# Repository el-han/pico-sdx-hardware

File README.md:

# Pico SDX

Pico SDX is a Software Defined HF Transceiver.

## Related Projects

- [uSDX](https://github.com/threeme3/usdx): ATmega 328P based SSB Transceiver. Large Arduino source file, no hardware sources, only schematics
- [(tr)uSDX](https://dl2man.de/): Implementation of uSDX by DL2MAN. No hardware sources, only schematics
- [uSDX-x](https://github.com/KD9PDP/uSDX-x): uSDX implementation with KiCAD hardware sources and JLCPCB friendly manufacturing data. ATmega328P based and compatible to uSDX. **Looks like a good starting point**
- [uSDR-pico](https://github.com/ArjanteMarvelde/uSDR-pico): RP2040 based SSB Transceiver. Highly experimental according to author. Pico SDK based Firmware, Eagle hardware sources. **Looks like a good starting point**
- [Blueberry SDR](http://www.andreadrian.de/sdr/Blueberry_SDR_schematics.html) experiments with different designs and components
- [YU1MLs SDRs](https://web.archive.org/web/20200227193146/http://yu1lm.qrpradio.com/sdr%20rx%20yu1lm.htm) many RX, TX and TRX designs
- [Teensy SDR](https://www.pjrc.com/convolution-software-defined-radio/) Teensy based sdr with waterfall diagram

## Related resources

- [Barbaros Aşuroğlu](https://antrak.org.tr/author/barbarosasuroglu/) has built an own uSDX implementation and many other projects.
- [QRP labs](https://www.qrp-labs.com/lpfkit.html) sells low pass and band pass filter modules for all HF bands
- [QRP labs](https://www.qrp-labs.com/synth/ms5351m.html) comparison between the clock generators Si5351A (Silicon labs) and MS5351M (Relmon) regarding usage in SDRs
- [Calculate your locator](https://dxcluster.ha8tks.hu/hamgeocoding/)

## technical background

- [Dan Tayloe](https://www.norcalqrp.org/files/Tayloe_mixer_x3a.pdf) brief description of the operation of quadratur mixers
- Gerald Youngbloods QEX articles [1](https://www.arrl.org/files/file/Technology/tis/info/pdf/020708qex013.pdf), [2](https://www.arrl.org/files/file/Technology/tis/info/pdf/020910qex010.pdf), [3](https://www.arrl.org/files/file/Technology/tis/info/pdf/021112qex027.pdf) and [4](http://www.arrl.org/files/file/Technology/tis/info/pdf/030304qex020.pdf) very good, detailed and comprehensive description of SDR projects for ham radio operators and additional [ARRL SDR](http://www.arrl.org/software-defined-radio) resources
- Walla Walla University projects: [Paper](http://fweb.wallawalla.edu/~frohro/ClassHandouts/Electronics/A%20Comparison%20of%20Affordable,%20Self-Assembled%20%20Software-Defined%20Radio%20Receivers%20Using%20Quadrature%20Sampling%20Down-Conversion.pdf), [Talk](https://www.youtube.com/watch?v=UoL1Qzaw2H0&t=217s),[Jordyn Watkins Wiki](https://github.com/greenjacketgirl/SDR_Receiver/wiki), [Caleb Froelichs Wiki](https://github.com/froeca/Software-Defined-Radio/), [Konrad MacClure](https://github.com/KonradMcClure/SDR_Receiver) and [SMD Version by Caleb Nelson](https://github.com/Dizzerin/Software-Defined-Radio)with detailed explanations, simulations, design decisions and tests
- [Burkhard Kainkas](https://www.b-kainka.de/iqrx.htm) experiments with iq mixers
- [devttys0](https://www.youtube.com/watch?v=JuuKF1RFvBM) video on explanations of the function of the tayloe mixer
- [w2aew](https://www.youtube.com/watch?v=Mm7WfVzr1ao) video on RF-mixer basics
- [BPF design for HF-Tranceiver](https://www.arrl.org/files/file/Technology/tis/info/pdf/8809017.pdf)
- [devttys0](https://www.youtube.com/watch?v=1sq8Cvju2Oo) video on practical filter design and construction

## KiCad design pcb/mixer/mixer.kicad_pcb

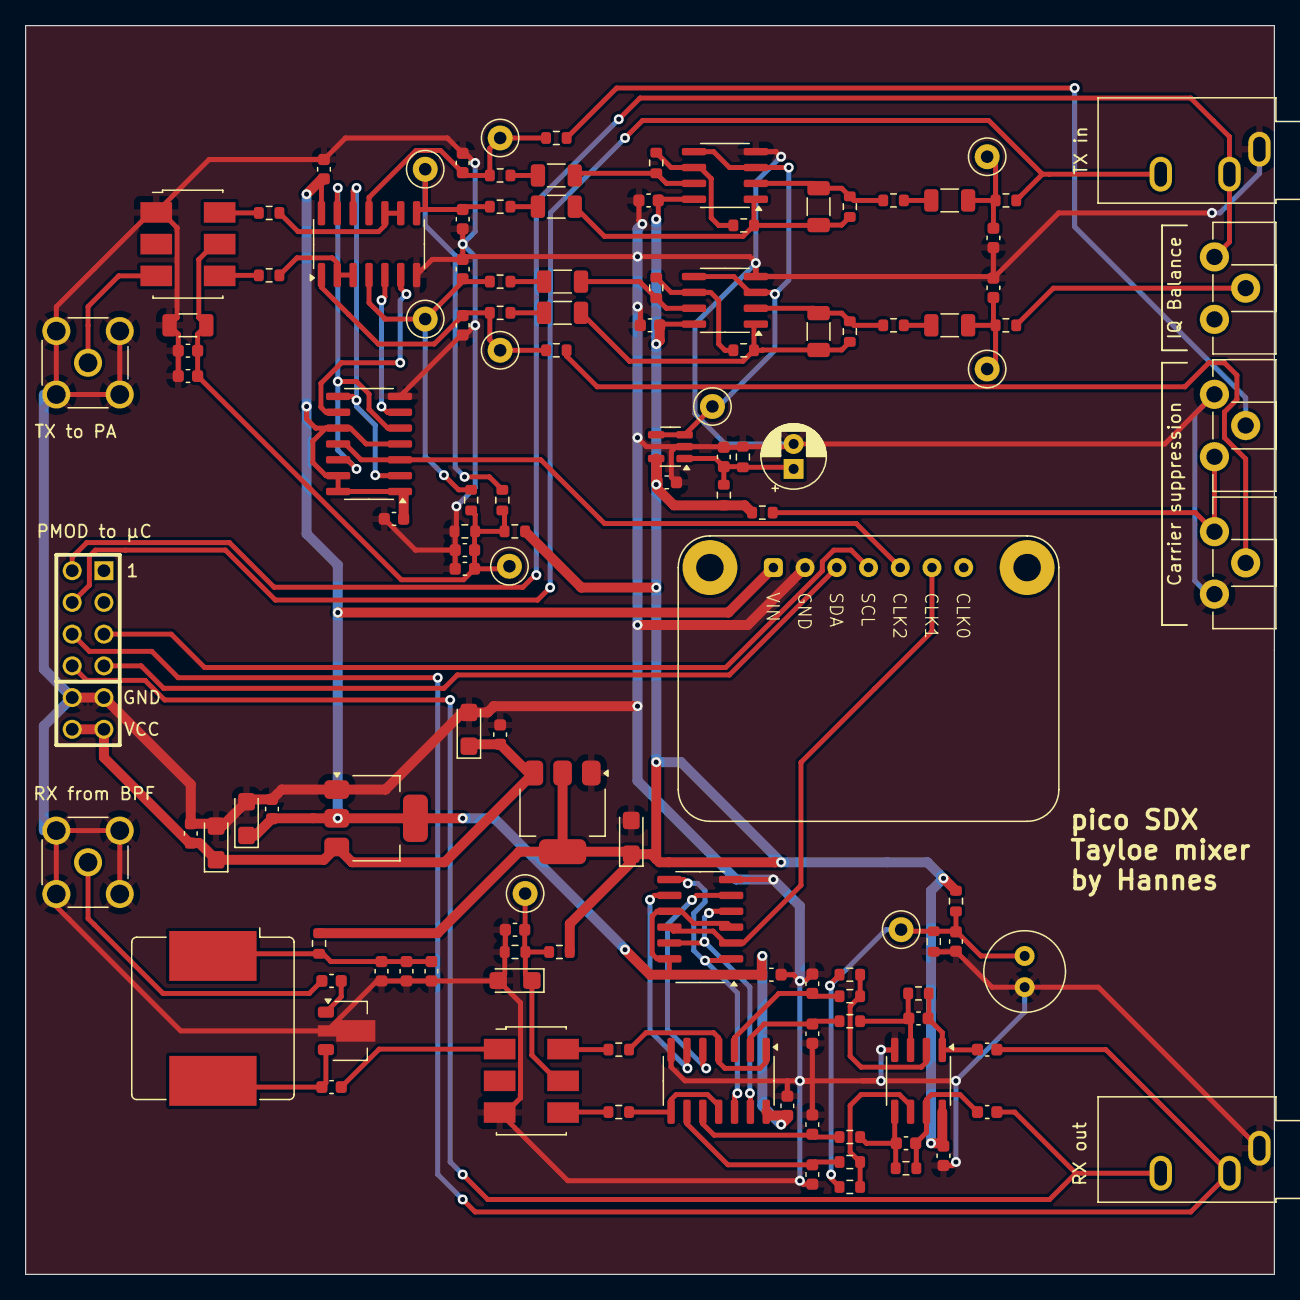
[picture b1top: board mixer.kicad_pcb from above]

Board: 2 copper layers, 100.0 x 100.0 mm, 126 parts (0 on the bottom side), 73 nets.

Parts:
C1, C2, C7, C14, C17, C19, C20, C32, C38, C39, C40, C42, C43, C44, C45, C51: 100nF; C_0603_1608Metric
C3, C4, C5, C6, C21: 1µF; CP_EIA-3216-18_Kemet-A
C8, C9, C10, C11, C33, C34, C35, C36: 22nF; C_0603_1608Metric
C12, C13: 330pF; C_0603_1608Metric
C15, C16, C46, C50: 1µF; C_0603_1608Metric
C18, C41: 10nF; C_0603_1608Metric
C22: 330µF; C_Radial_D6.3mm_H11.0mm_P2.50mm
C23, C24: 220pF; C_0603_1608Metric
C25, C26, C27, C28, C29, C30, C37: 10µF; C_1206_3216Metric
C31: 47µF; CP_Radial_D5.0mm_P2.00mm
C47: 2.2µF; C_0603_1608Metric
C48: 1000pF; C_0603_1608Metric
C49: 100pF; C_0603_1608Metric
C52, C53: 100pF; C_1206_3216Metric
J4, J5: Conn_Coaxial; SMA_Molex_73251-2200_Horizontal
J6, J7: AudioJack3; Jack_3.5mm_CUI_SJ1-3533NG_Horizontal
L1: 27µH; L_Bourns_SRR1208_12.7x12.7mm
P1: PMOD-Device-x2-Type-Generic-Alt; pmod_pin_array_6x2
R1, R2: 82R; R_0603_1608Metric
R3, R4, R5, R6: 100R; R_0603_1608Metric
R7, R8, R9, R10, R15, R29, R30, R31, R32, R34, R35: 2.2k; R_0603_1608Metric
R11, R12, R13, R14: 1k; R_0603_1608Metric
R16: 2.7k; R_0603_1608Metric
R17, R18, R19, R20, R25, R26, R37, R38: 10k; R_0603_1608Metric
R21, R22, R23, R24: 51R; R_0603_1608Metric
R27, R28: 47R; R_0603_1608Metric
R33: 1.2k; R_0603_1608Metric
R36: 1.8R; R_0603_1608Metric
R39, R40: 7.5k; R_0603_1608Metric
RV1, RV2, RV3: 1k; Potentiometer_Piher_PT-10-H01_Horizontal
T1: T-622; Transformer_MiniCircuits_ADT1-6T+
T2: Transformer_SP_1S; Transformer_MiniCircuits_ADT1-6T+
TP3: RX_TR_Midpoint; TestPoint_Loop_D1.80mm_Drill1.0mm_Beaded
TP4: RX_OPAMP_Midpoint; TestPoint_Loop_D1.80mm_Drill1.0mm_Beaded
TP5, TP6, TP7, TP8, TP9, TP10, TP11, TP12: TestPoint; TestPoint_Loop_D1.80mm_Drill1.0mm_Beaded
U1: Module_Si5351
U5: LT1117-5.0; SOT-223-3_TabPin2
U6, U9: 74HC74; SOIC-14_3.9x8.7mm_P1.27mm
U7, U12: 4066; SOIC-14_3.9x8.7mm_P1.27mm
U8: OPA2350; SOIC-8_3.9x4.9mm_P1.27mm
U10, U14: OPA1602; SOIC-8_3.9x4.9mm_P1.27mm
U11: LM321; SOT-23-5
U13: HMC589A; SOT-89-3
U17: LT1117-3.3; SOT-223-3_TabPin2

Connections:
+3.3V: C5.1, C7.1, C14.1, C17.1, C40.1, C42.1, U1.1 (VIN), U6.1 (~R), U6.4 (~S), U6.10 (~S), U6.13 (~R), U6.14 (VCC), U7.14 (VDD), U9.1 (~R), U9.4 (~S), U9.10 (~S), U9.13 (~R), U9.14 (VCC), U12.14 (VDD), U17.2 (VO)
+5VA: C6.1, C20.1, C38.1, C44.1, C51.1, R11.1, R13.1, R25.1, R31.1, R33.1, R36.2, U5.2 (VO), U8.8 (V+), U10.8 (V+), U11.5 (V+), U14.8 (V+)
+12V: C1.1, C2.1, C3.1, C4.1, P1.6, P1.12, U5.3 (VI), U17.3 (VI)
/Buffer Amplifier/RF in: C46.1, J4.1 (In)
/Buffer Amplifier/RF out: C50.2, T1.1 (Primary)
/Downconverter/2.5V_OPAMP: C19.1, C22.1, R8.2, R10.2, R13.2, R14.1, TP4.1
/Downconverter/2.5V_TR: C18.1, C21.1, R11.2, R12.1, T1.5 (Secondary_CT), TP3.1
/Downconverter/CLK_I: U6.5 (Q), U6.12 (D), U7.13
/Downconverter/CLK_Q: U6.9 (Q), U7.6
/Downconverter/~CLK_I: U6.6 (~Q), U7.5
/Downconverter/~CLK_Q: U6.2 (D), U6.8 (~Q), U7.12
/Upconverter/2.5V: TP11.1, U10.3 (+), U10.5 (+), U11.3 (-), U11.4, U14.3 (+), U14.5 (+)
/Upconverter/BIAS: C37.1, C39.1, C41.1, C43.1, C45.1, R30.2, R31.2, R32.1, R34.1, T2.5 (Secondary_CT), TP12.1
/Upconverter/BIAS_I: C33.1, R21.2, R29.1, TP7.1, U12.1
/Upconverter/BIAS_Q: C35.1, R23.2, R34.2, TP9.1, U12.8
/Upconverter/CLK_I: U9.5 (Q), U9.12 (D), U12.13
/Upconverter/CLK_Q: U9.9 (Q), U12.6
/Upconverter/TX_OUT: J5.1 (In), T2.3 (Primary_dot)
/Upconverter/~BIAS_I: C34.1, R22.2, R30.1, TP8.1, U12.4
/Upconverter/~BIAS_Q: C36.1, R24.2, R35.2, TP10.1, U12.11
/Upconverter/~CLK_I: U9.6 (~Q), U12.5
/Upconverter/~CLK_Q: U9.2 (D), U9.8 (~Q), U12.12
GND: C1.2, C2.2, C3.2, C4.2, C5.2, C6.2, C7.2, C8.1, C9.1, C10.1, C11.1, C14.2, C17.2, C18.2, C19.2, C20.2, C21.2, C22.2, C23.2, C24.2, C31.2, C32.2, C33.2, C34.2, C35.2, C36.2, C37.2, C38.2, C39.2, C40.2, C41.2, C42.2, C43.2, C44.2, C45.2, C47.2, C48.2, C49.2, C51.2, J4.2 (Ext), J5.2 (Ext), J6.S, J7.S, P1.5, P1.11, R12.2, R14.2, R26.2, R32.2, RV2.3, RV3.1, T1.3 (Primary_dot), T2.1 (Primary), U1.2 (GND), U5.1 (GND), U6.7 (GND), U7.7 (VSS), U8.4 (V-), U9.7 (GND), U10.4 (V-), U11.2 (V-), U12.7 (VSS), U13.2 (GND), U14.4 (V-), U17.1 (GND)
unnamed: C8.2, R3.1, U7.2
unnamed: C9.2, R4.1, U7.3
unnamed: C10.2, R5.1, U7.10
unnamed: C11.2, R6.1, U7.9
unnamed: C12.1, C15.2, R7.2, U8.1
unnamed: C13.1, C16.2, R9.2, U8.7
unnamed: C23.1, C25.1, R15.2, TP5.1
unnamed: C24.1, C26.1, R16.2, TP6.1
unnamed: C25.2, R39.1
unnamed: C26.2, R40.1
unnamed: C27.1, C52.2, R17.1, R38.2, U10.1
unnamed: C27.2, R21.1
unnamed: C28.1, R19.2, U10.7
unnamed: C28.2, R22.1
unnamed: C29.1, C53.2, R18.1, R37.2, U14.1
unnamed: C29.2, R23.1
unnamed: C30.1, R20.2, U14.7
unnamed: C30.2, R24.1
unnamed: C46.2, U13.1
unnamed: C47.1, C48.1, C49.1, L1.1, R36.1
unnamed: C50.1, L1.2, U13.3
unnamed: R1.1, T1.6 (Secondary_dot)
unnamed: R1.2, U7.1, U7.4
unnamed: R2.1, T1.4 (Secondary_dot)
unnamed: R2.2, U7.8, U7.11
unnamed: R15.1, RV1.2
unnamed: R27.1, U12.2, U12.3
unnamed: R27.2, T2.4 (Secondary_dot)
unnamed: R28.1, U12.9, U12.10
unnamed: R28.2, T2.6 (Secondary_dot)
unnamed: R29.2, RV2.2
unnamed: R33.2, RV2.1, RV3.3
unnamed: R35.1, RV3.2
unnamed: C12.2, R3.2, R7.1, U8.3 (+)
unnamed: R4.2, R8.1, U8.2 (-)
unnamed: C13.2, R5.2, R9.1, U8.5 (+)
unnamed: R6.2, R10.1, U8.6 (-)
unnamed: C52.1, R38.1, R39.2, U10.2 (-)
unnamed: R17.2, R19.1, U10.6 (-)
unnamed: C31.1, C32.1, R25.2, R26.1, U11.1 (+)
unnamed: C53.1, R37.1, R40.2, U14.2 (-)
unnamed: R18.2, R20.1, U14.6 (-)
RX_I: C15.1, J6.T, P1.9
RX_LO: U1.6 (CLK1), U6.3 (C), U6.11 (C)
RX_Q: C16.1, J6.R, P1.10
SCL: P1.3, U1.4 (SCL)
SDA: P1.4, U1.3 (SDA)
TX_I: J7.T, P1.7, RV1.1
TX_LO: U1.5 (CLK2), U9.3 (C), U9.11 (C)
TX_Q: J7.R, P1.8, R16.1

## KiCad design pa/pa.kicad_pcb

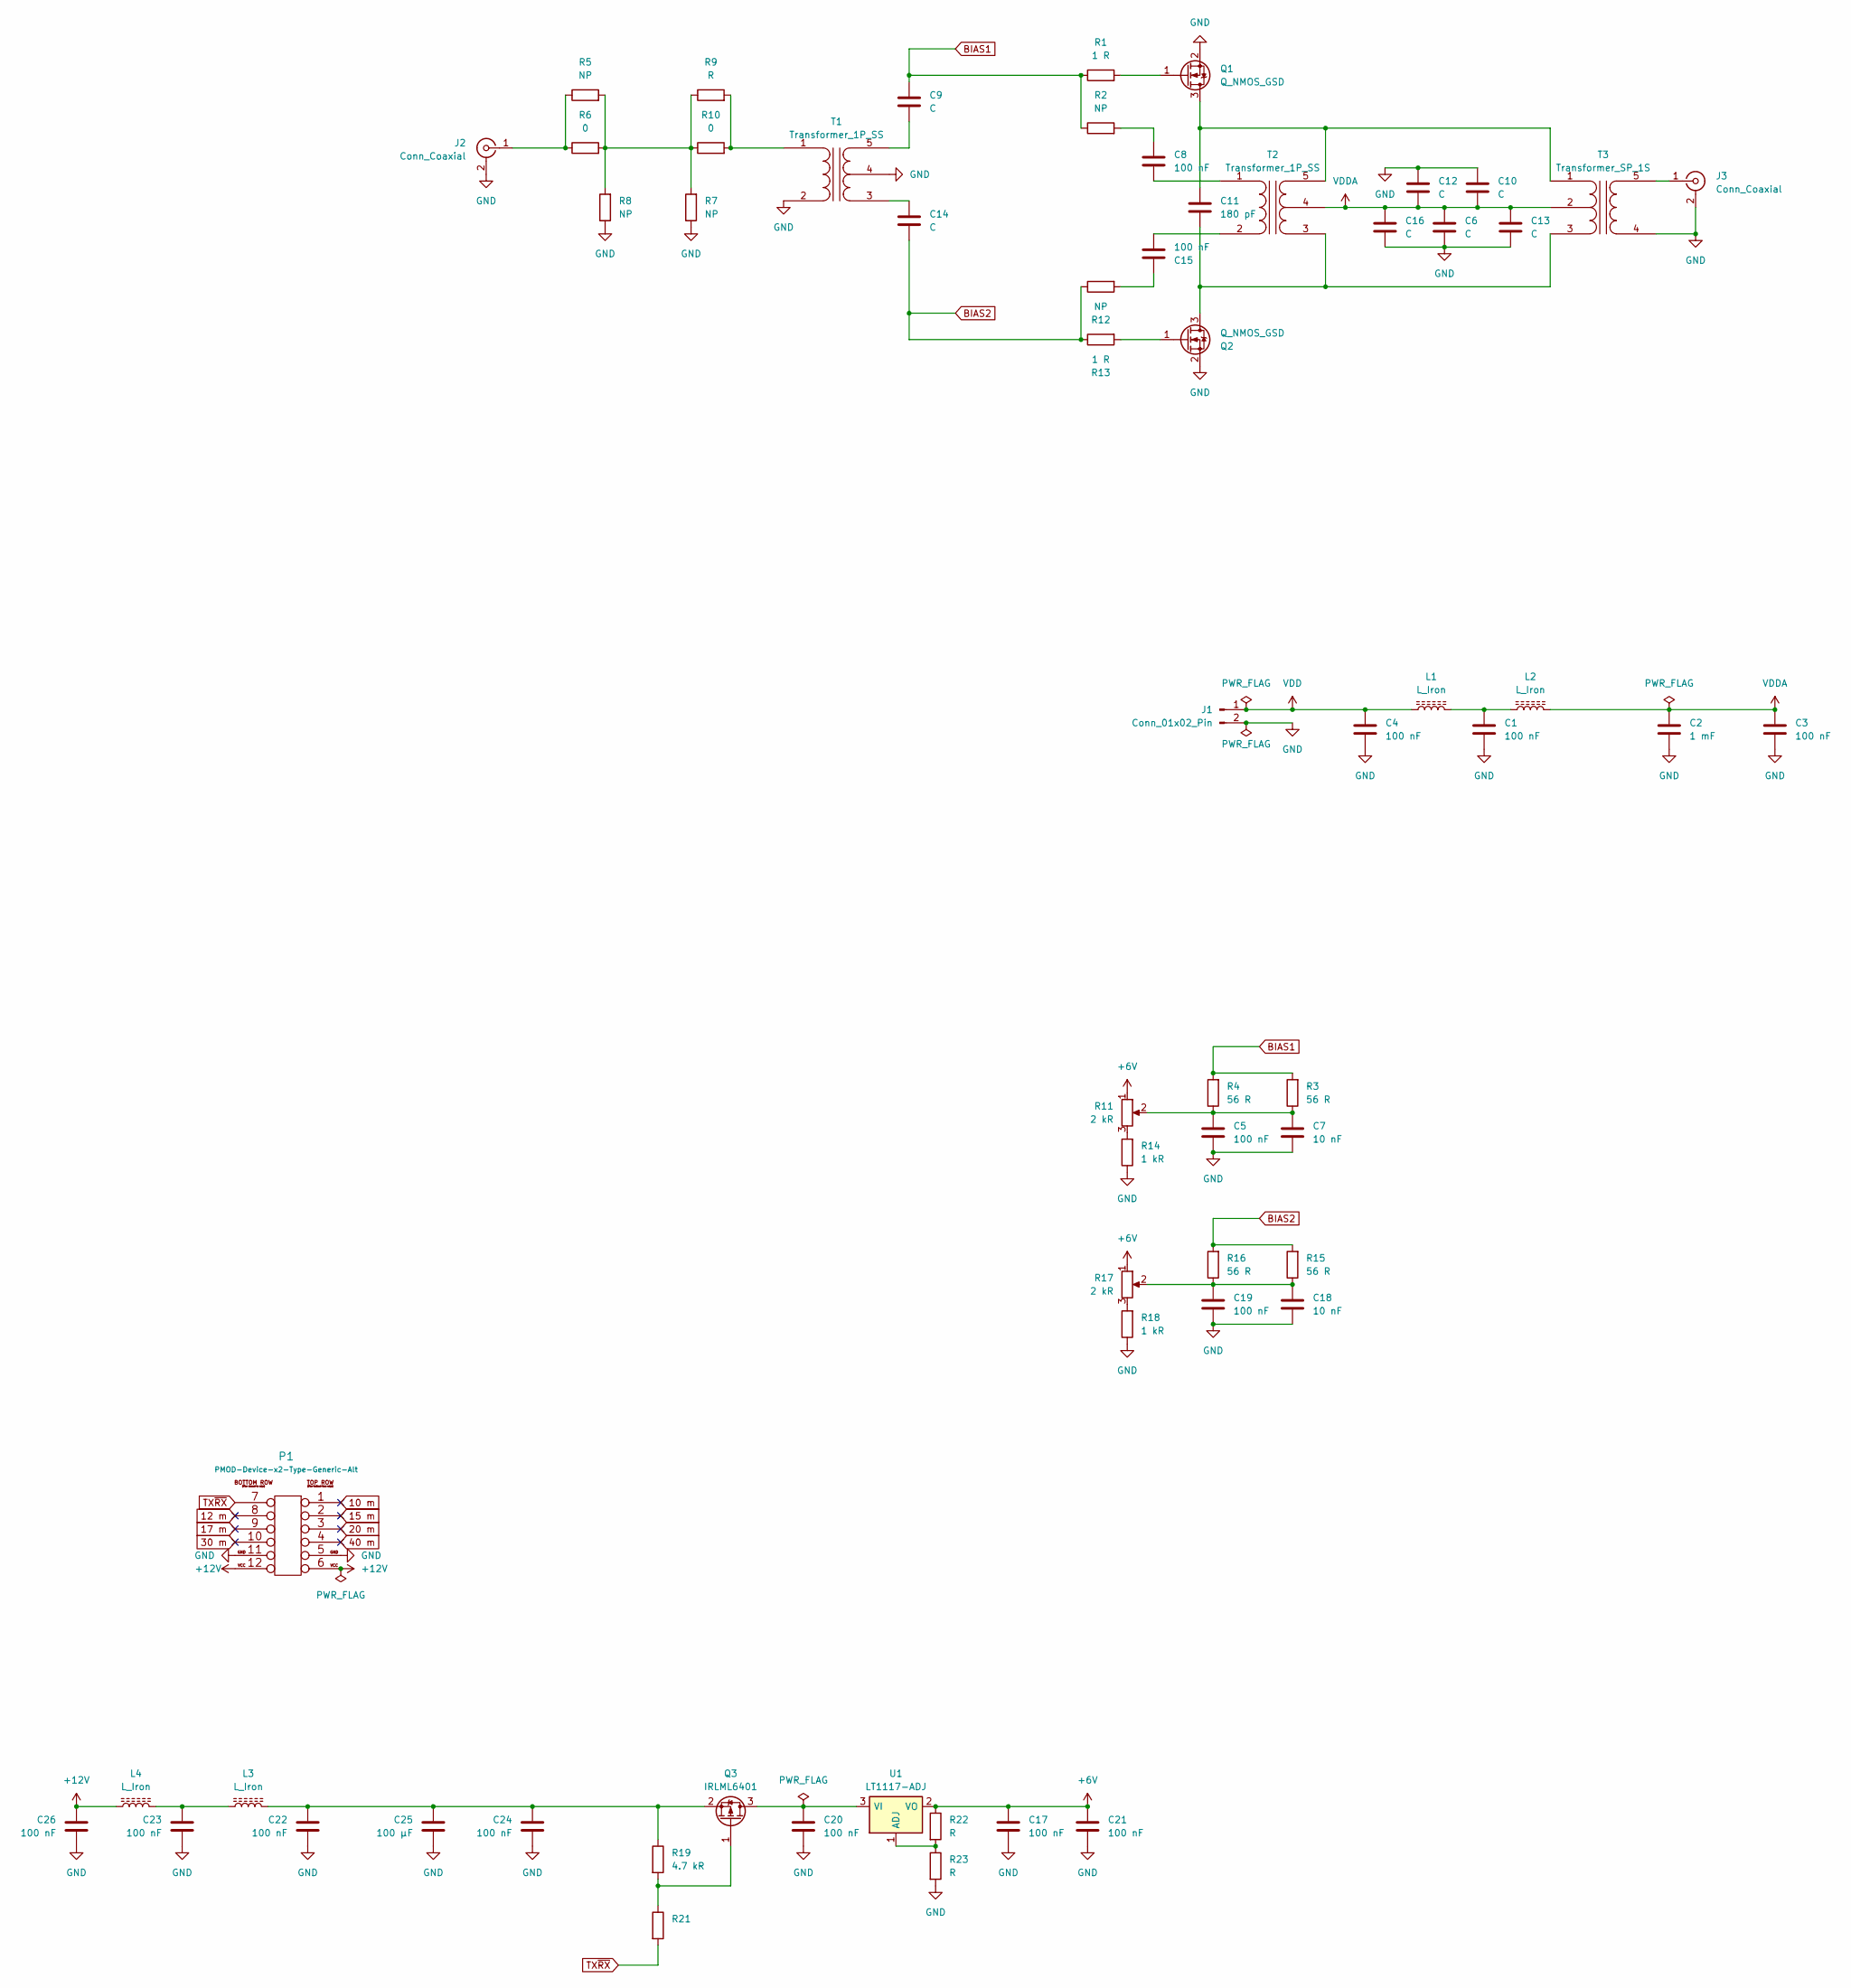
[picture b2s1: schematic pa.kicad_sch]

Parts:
C1, C3, C4, C5, C8, C15, C17, C19, C20, C21, C22, C23, C24, C26: 100 nF; C_1206_3216Metric
C2: 1 mF; CAP_H32F_CND
C6, C9, C10, C12, C13, C14, C16: C; C_1206_3216Metric
C7, C18: 10 nF; C_1206_3216Metric
C11: 180 pF; C_1210_3225Metric
C25: 100 µF; CP_Elec_8x10
J1: Conn_01x02_Pin; JST_VH_S2P-VH_1x02_P3.96mm_Horizontal
J2, J3: Conn_Coaxial; SMA_Molex_73251-2200_Horizontal
L1, L2: L_Iron; L_Axial_L11.0mm_D4.5mm_P7.62mm_Vertical_Fastron_MECC
L3, L4: L_Iron; L_Axial_L7.0mm_D3.3mm_P5.08mm_Vertical_Fastron_MICC
P1: PMOD-Device-x2-Type-Generic-Alt; pmod_pin_array_6x2
Q1, Q2: Q_NMOS_GSD; TO-220F-3_Horizontal_TabDown
Q3: IRLML6401; SOT-23
R1, R13: 1 R; R_1206_3216Metric
R2, R5, R7, R8, R12: NP; R_1206_3216Metric
R3, R4, R15, R16: 56 R; R_1206_3216Metric
R6, R10: 0; R_1206_3216Metric
R9: R; R_1206_3216Metric
R11, R17: 2 kR; Potentiometer_Bourns_3296W_Vertical
R14, R18: 1 kR; R_1206_3216Metric
R19: 4.7 kR; R_1206_3216Metric
R21: R_1206_3216Metric
R22, R23: R; R_0603_1608Metric
T1: Transformer_1P_SS; Transformer 1
T2: Transformer_1P_SS; Transformer 2
T3: Transformer_SP_1S; Transformer 3
U1: LT1117-ADJ; SOT-223-3_TabPin2

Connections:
10 m: P1.1
12 m: P1.8
15 m: P1.2
17 m: P1.9
20 m: P1.3
30 m: P1.10
40 m: P1.4
+6V: C17.1, C21.1, R11.1, R17.1, R22.1, U1.2 (VO)
+12V: C26.1, L4.1, P1.6, P1.12
BIAS1: C9.1, R1.1, R2.1, R3.2, R4.2
BIAS2: C14.2, R12.1, R13.1, R15.2, R16.2
GND: C1.2, C2.2, C3.2, C4.2, C5.2, C6.2, C7.2, C10.1, C12.1, C13.2, C16.2, C17.2, C18.2, C19.2, C20.2, C21.2, C22.2, C23.2, C24.2, C25.2, C26.2, J1.2, J2.2 (Ext), J3.2 (Ext), P1.5, P1.11, Q1.2 (S), Q2.2 (S), R7.1, R8.1, R14.1, R18.1, R23.2, T1.2 (AB), T1.4 (SC), T3.4 (S1)
unnamed: C1.1, L1.1, L2.1
unnamed: C5.1, C7.1, R3.1, R4.1, R11.2
unnamed: C8.1, R2.2
unnamed: C15.1, R12.2
unnamed: C18.1, C19.1, R15.1, R16.1, R17.2
unnamed: C23.1, L3.1, L4.2
unnamed: J2.1 (In), R5.1, R6.1
unnamed: J3.1 (In), T3.5 (S2)
unnamed: C11.1, Q1.3 (D), T2.5 (SB), T3.1 (PR1)
unnamed: Q1.1 (G), R1.2
unnamed: C11.2, Q2.3 (D), T2.3 (SA), T3.3 (PR2)
unnamed: Q2.1 (G), R13.2
unnamed: C20.1, Q3.3 (D), U1.3 (VI)
unnamed: Q3.1 (G), R19.2, R21.1
unnamed: C22.1, C24.1, C25.1, L3.2, Q3.2 (S), R19.1
unnamed: R5.2, R6.2, R7.2, R8.2, R9.1, R10.1
unnamed: R11.3, R14.2
unnamed: R17.3, R18.2
unnamed: R9.2, R10.2, T1.1 (AA)
unnamed: C14.1, T1.3 (SA)
unnamed: C9.2, T1.5 (SB)
unnamed: C8.2, T2.1 (AA)
unnamed: C15.2, T2.2 (AB)
unnamed: R22.2, R23.1, U1.1 (ADJ)
TX~RX: P1.7, R21.2
VDD: C4.1, J1.1, L1.2
VDDA: C2.1, C3.1, C6.1, C10.2, C12.2, C13.1, C16.1, L2.2, T2.4 (SC), T3.2 (PM)

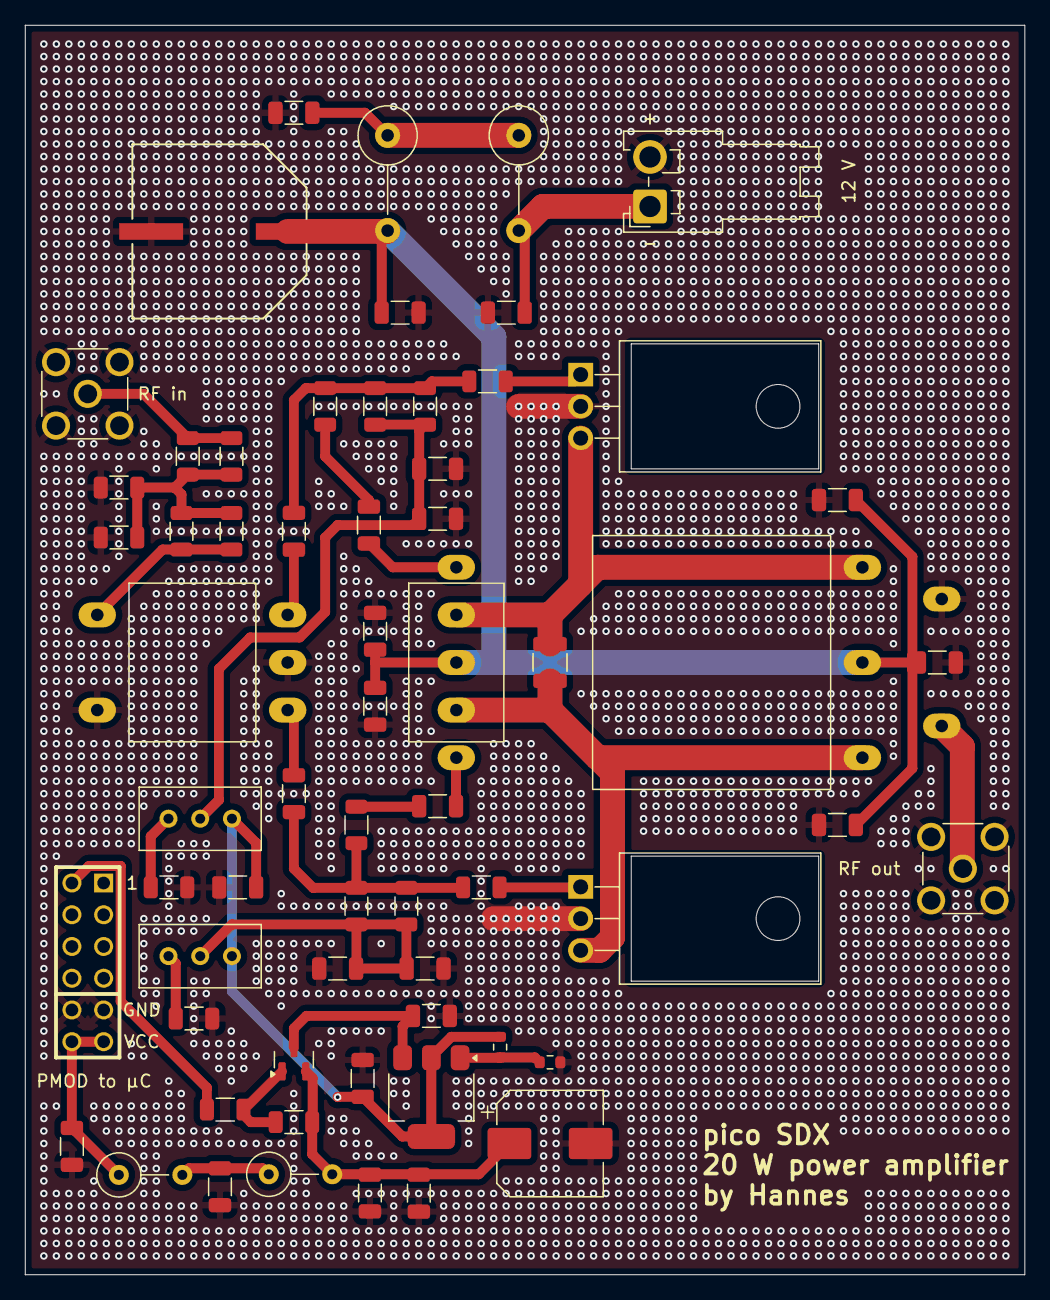
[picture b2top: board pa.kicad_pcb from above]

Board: 2 copper layers, 80.0 x 100.0 mm, 63 parts (0 on the bottom side), 32 nets.

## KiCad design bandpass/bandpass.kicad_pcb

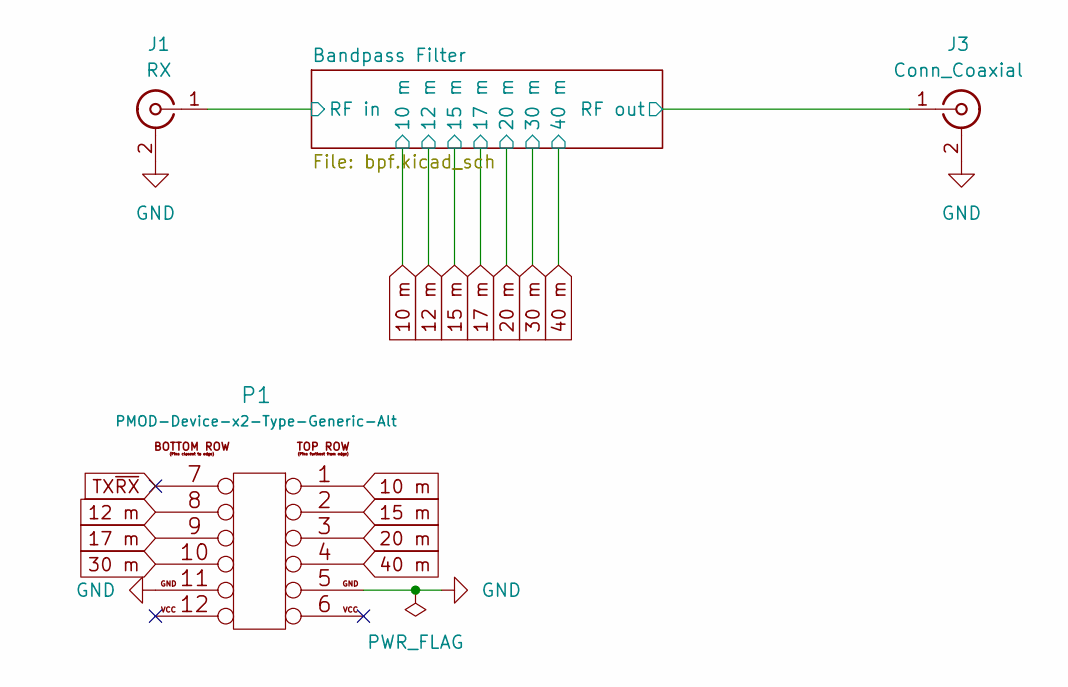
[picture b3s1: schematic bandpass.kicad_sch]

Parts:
J1: RX; SMA_Molex_73251-2200_Horizontal
J3: Conn_Coaxial; SMA_Molex_73251-2200_Horizontal
P1: PMOD-Device-x2-Type-Generic-Alt; pmod_pin_array_6x2

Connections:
+12V: P1.6, P1.12; also elsewhere on the board
/Bandpass Filter/RF in: J1.1 (In); also elsewhere on the board
/Bandpass Filter/RF out: J3.1 (In); also elsewhere on the board
TX~RX: P1.7

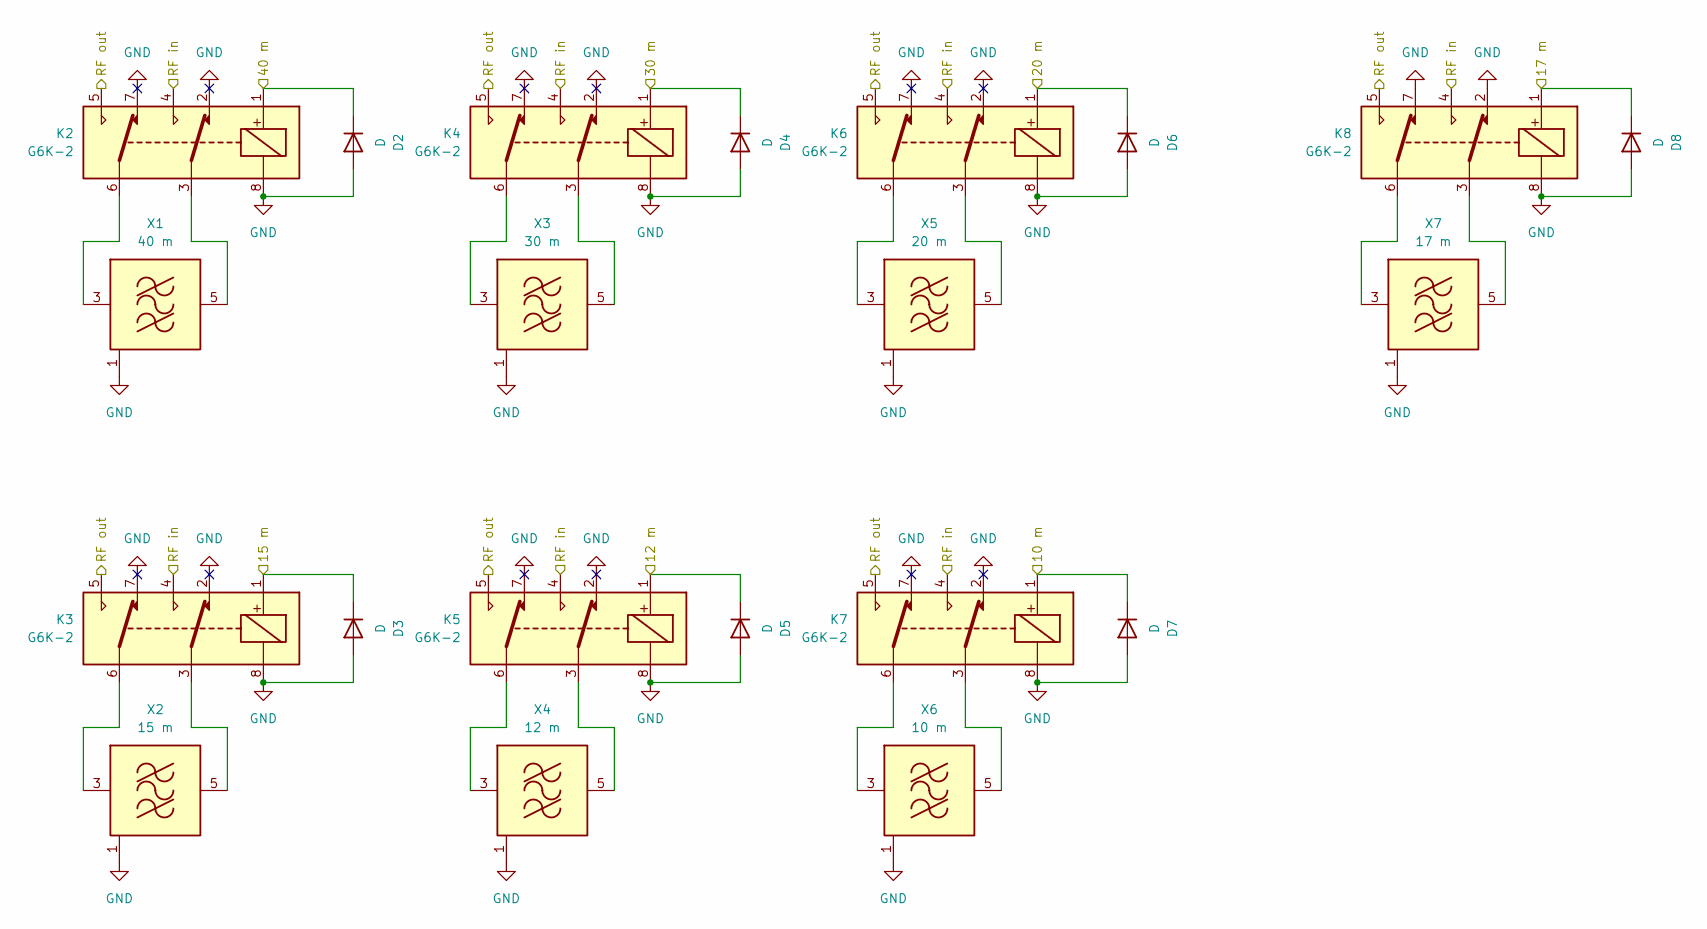
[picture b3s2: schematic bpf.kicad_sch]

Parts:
D2, D3, D4, D5, D6, D7, D8: D; D_SOD-128
K2, K3, K4, K5, K6, K7, K8: G6K-2; Relay_DPDT_Omron_G6K-2P
X1: 40 m; Filter Module
X2: 15 m; Filter Module
X3: 30 m; Filter Module
X4: 12 m; Filter Module
X5: 20 m; Filter Module
X6: 10 m; Filter Module
X7: 17 m; Filter Module

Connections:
+12V: D2.1 (K), D3.1 (K), D4.1 (K), D5.1 (K), D6.1 (K), D7.1 (K), D8.1 (K), K2.1, K3.1, K4.1, K5.1, K6.1, K7.1, K8.1; also elsewhere on the board
/Bandpass Filter/RF in: K2.4, K3.4, K4.4, K5.4, K6.4, K7.4, K8.4; also elsewhere on the board
/Bandpass Filter/RF out: K2.5, K3.5, K4.5, K5.5, K6.5, K7.5, K8.5; also elsewhere on the board
unnamed: K2.3, X1.5 (OUT), X1.6 (OUT)
unnamed: K2.6, X1.3 (IN), X1.4 (IN)
unnamed: K3.3, X2.5 (OUT), X2.6 (OUT)
unnamed: K3.6, X2.3 (IN), X2.4 (IN)
unnamed: K4.3, X3.5 (OUT), X3.6 (OUT)
unnamed: K4.6, X3.3 (IN), X3.4 (IN)
unnamed: K5.3, X4.5 (OUT), X4.6 (OUT)
unnamed: K5.6, X4.3 (IN), X4.4 (IN)
unnamed: K6.3, X5.5 (OUT), X5.6 (OUT)
unnamed: K6.6, X5.3 (IN), X5.4 (IN)
unnamed: K7.3, X6.5 (OUT), X6.6 (OUT)
unnamed: K7.6, X6.3 (IN), X6.4 (IN)
unnamed: K8.3, X7.5 (OUT), X7.6 (OUT)
unnamed: K8.6, X7.3 (IN), X7.4 (IN)

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
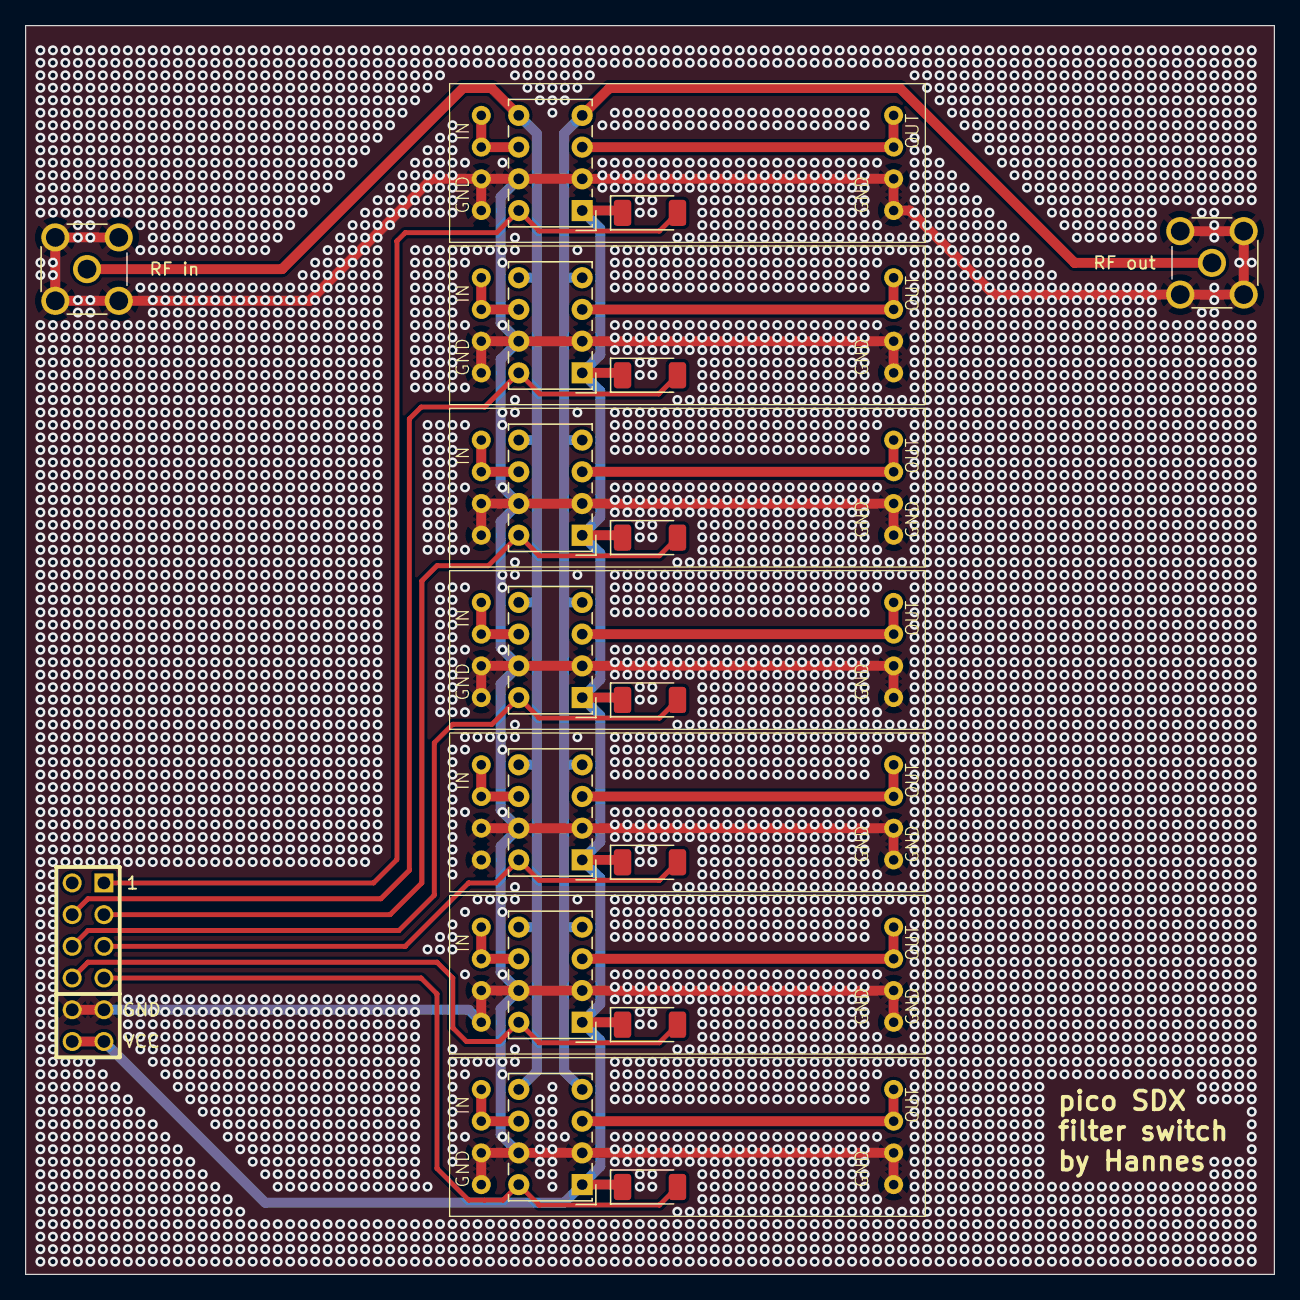
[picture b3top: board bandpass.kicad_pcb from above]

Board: 2 copper layers, 100.0 x 100.0 mm, 24 parts (0 on the bottom side), 25 nets.
